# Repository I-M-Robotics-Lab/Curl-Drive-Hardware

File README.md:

# Curl-Drive: BLDC Motor Controller

This repository contains the hardware PCB design, schematics, and production files of the brushless motor FOC controller **Curl-Drive** developed by I'M Robotics Lab. 

The firmware is still under development, but the hardware has been validated with no major issues. Full version is planned to be released in early January. 

We welcome contributions from anyone! To get involved or ask questions, join our Discord server. 

Discord: https://discord.com/invite/WJuUWsy6DJ

Firmware (pre-release): https://github.com/I-M-Robotics-Lab/Curl-Drive-Firmware

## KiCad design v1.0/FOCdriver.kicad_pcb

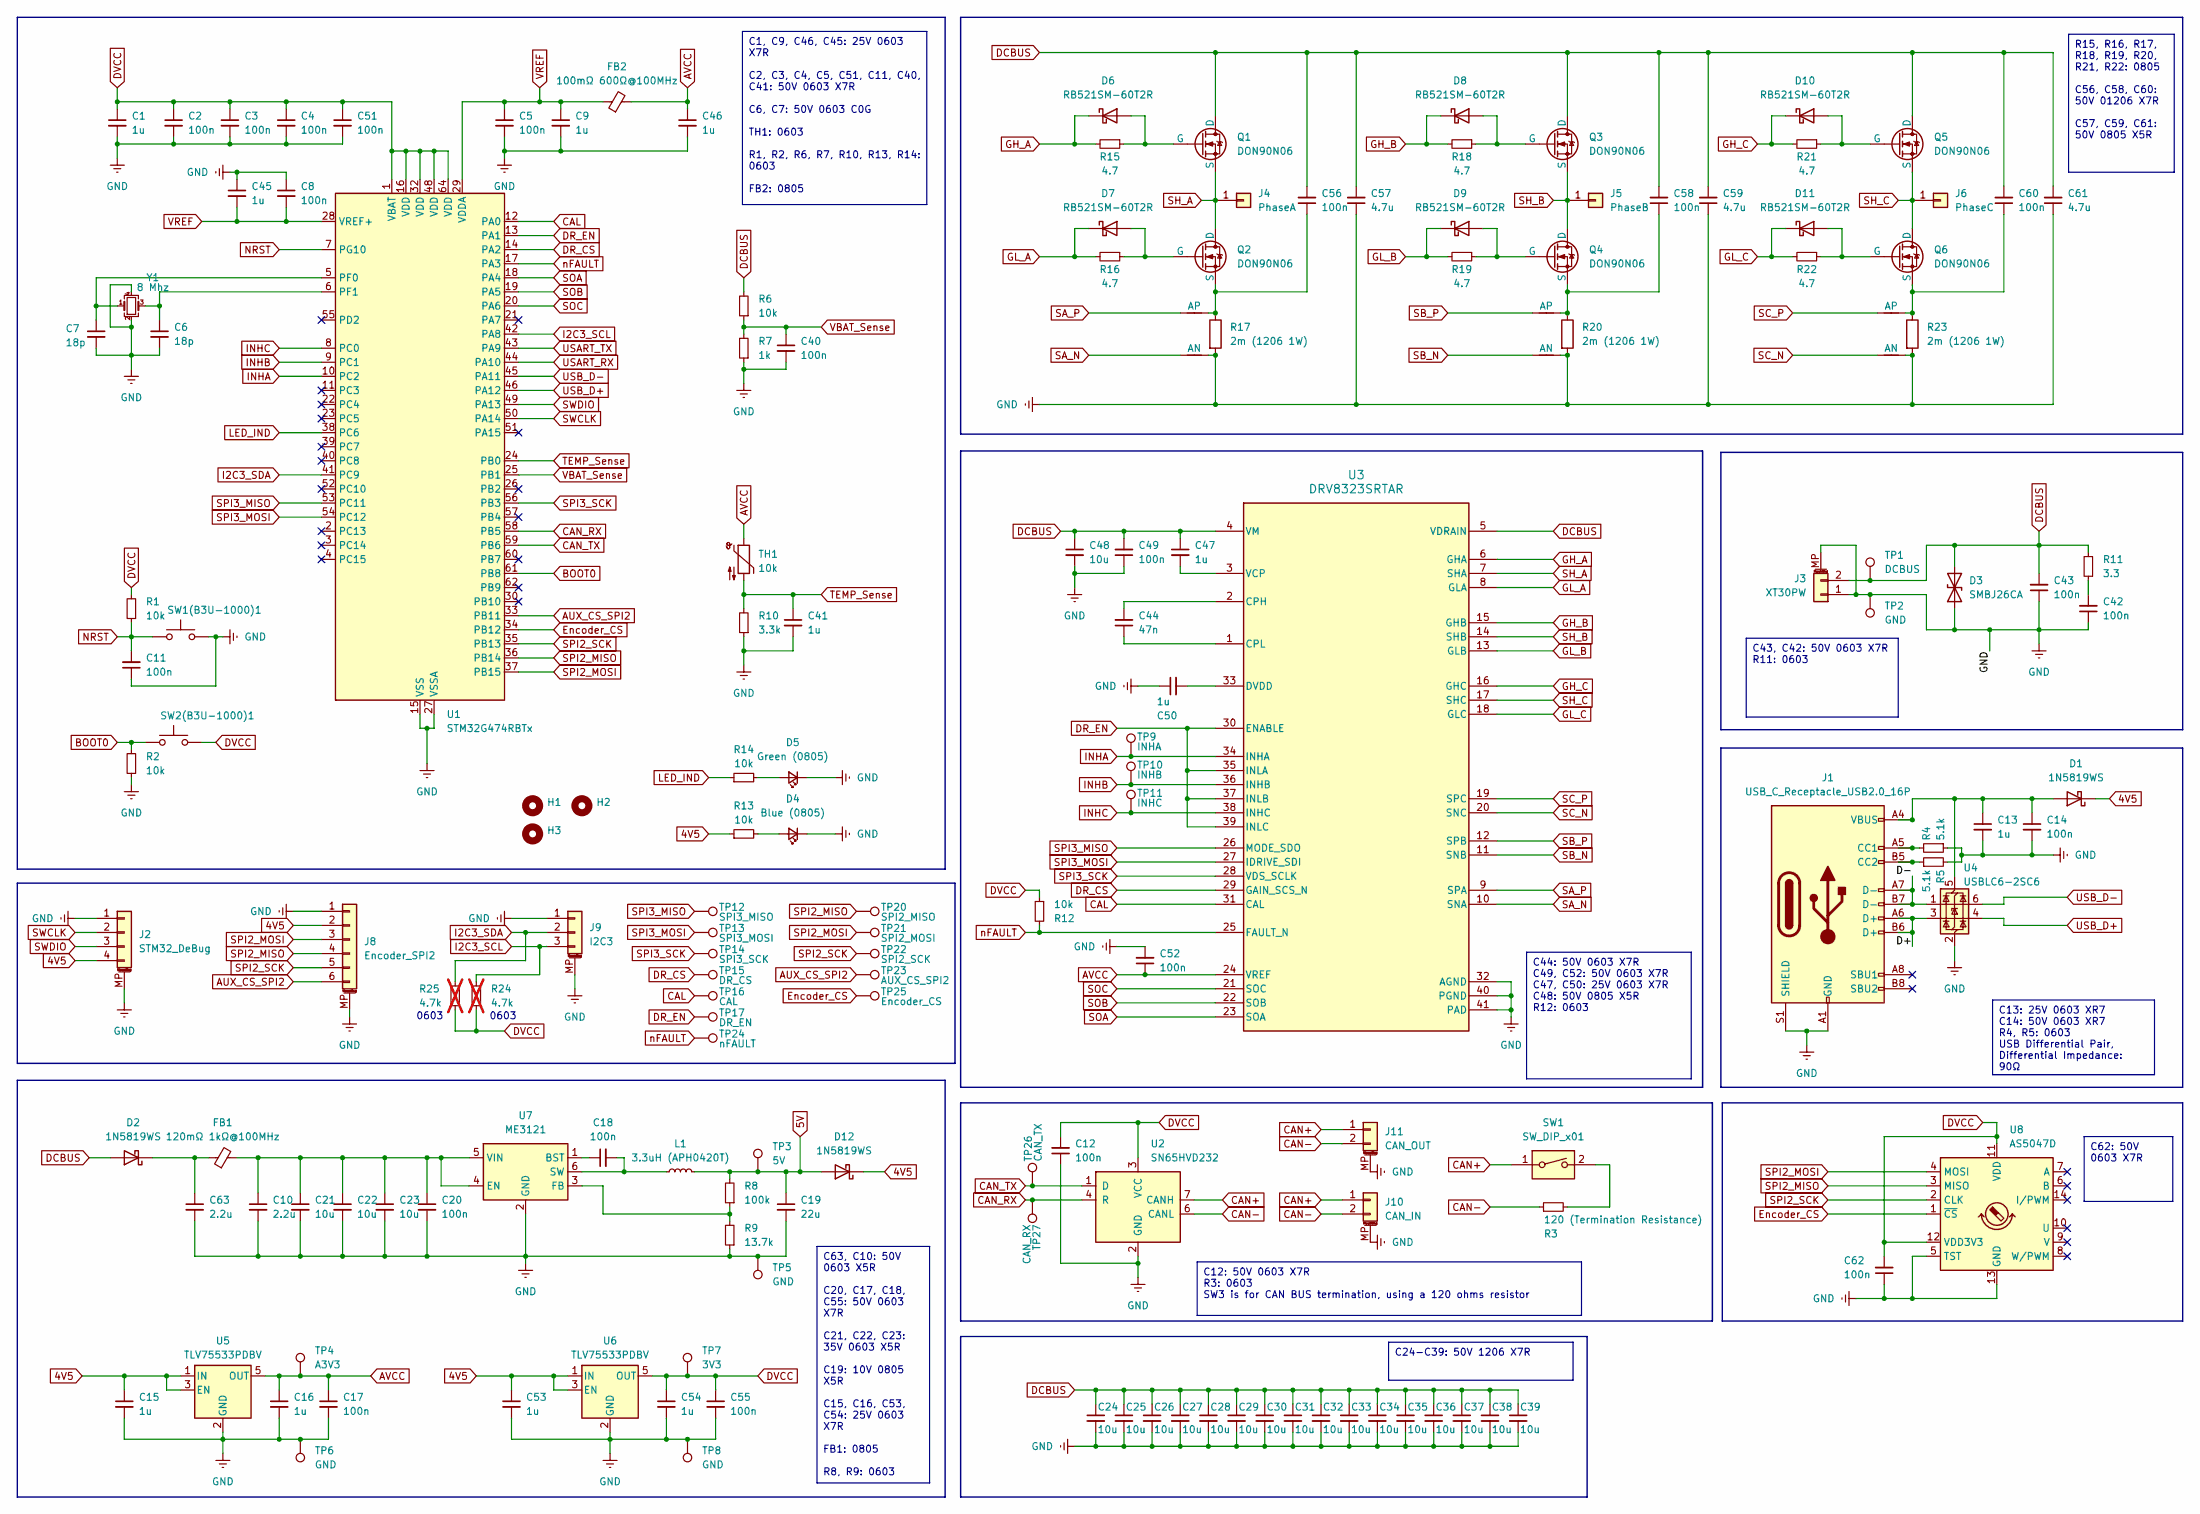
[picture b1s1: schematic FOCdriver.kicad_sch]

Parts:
C1, C9, C13, C15, C16, C41, C45, C46, C47, C50, C53, C54: 1u; C_0603_1608Metric
C2, C3, C4, C5, C8, C11, C12, C14, C17, C18, C20, C40, C42, C43, C49, C51, C52, C55, C62: 100n; C_0603_1608Metric
C6, C7: 18p; C_0603_1608Metric
C10, C63: 2.2u; C_0603_1608Metric
C19: 22u; C_0805_2012Metric
C21, C22, C23: 10u; C_0603_1608Metric
C24, C25, C26, C27, C28, C29, C30, C31, C32, C33, C34, C35, C36, C37, C38, C39: 10u; C_1206_3216Metric
C44: 47n; C_0603_1608Metric
C48: 10u; C_0805_2012Metric
C56, C58, C60: 100n; C_1206_3216Metric
C57, C59, C61: 4.7u; C_0805_2012Metric
D1, D2, D12: 1N5819WS; D_SOD-323
D3: SMBJ26CA; D_SMB
D4: Blue (0805); LED_0805_2012Metric
D5: Green (0805); LED_0805_2012Metric
D6, D7, D8, D9, D10, D11: RB521SM-60T2R; D_SOD-523
FB1: 120mΩ 1kΩ@100MHz; R_0805_2012Metric
FB2: 100mΩ 600Ω@100MHz; R_0805_2012Metric
H1, H2, H3: MountingHole_2.2mm_M2_DIN965_Pad
J1: USB_C_Receptacle_USB2.0_16P; USB_C_Receptacle_G-Switch_GT-USB-7010ASV
J2: STM32_DeBug; JST_SH_SM04B-SRSS-TB_1x04-1MP_P1.00mm_Horizontal
J3: XT30PW; AMASS_XT30PW-M_1x02_P2.50mm_Horizontal
J4: PhaseA; 4.5x4.5_pad
J5: PhaseB; 4.5x4.5_pad
J6: PhaseC; 4.5x4.5_pad
J8: Encoder_SPI2; JST_SH_SM06B-SRSS-TB_1x06-1MP_P1.00mm_Horizontal
J9: I2C3; JST_SH_SM03B-SRSS-TB_1x03-1MP_P1.00mm_Horizontal
J10: CAN_IN; JST_SH_SM02B-SRSS-TB_1x02-1MP_P1.00mm_Horizontal
J11: CAN_OUT; JST_SH_SM02B-SRSS-TB_1x02-1MP_P1.00mm_Horizontal
L1: 3.3uH (APH0420T); L_APV_APH0420
NT1, NT3, NT5: AP; NetTie-2
NT2, NT4, NT6: AN; NetTie-2
Q1, Q2, Q3, Q4, Q5, Q6: DON90N06; DFN-8-1EP_6x5mm_MOSFET
R1, R2, R6, R12, R13, R14: 10k; R_0603_1608Metric
R3: 120 (Termination Resistance); R_0603_1608Metric
R4, R5: 5.1k; R_0603_1608Metric
R7: 1k; R_0603_1608Metric
R8: 100k; R_0603_1608Metric
R9: 13.7k; R_0603_1608Metric
R10: 3.3k; R_0603_1608Metric
R11: 3.3; R_0603_1608Metric
R15, R16, R18, R19, R21, R22: 4.7; R_0603_1608Metric
R17, R20, R23: 2m (1206 1W); R_1206_3216Metric
R24, R25: 4.7k; R_0603_1608Metric; not fitted
SW1: SW_DIP_x01; SW_SPST_DSHP-01-TJ-GER
SW1(B3U-1000)1, SW2(B3U-1000)1: SW_Push; SW_SPST_B3U-1000P
TH1: 10k; R_0603_1608Metric
TP1: DCBUS; TestPoint_Pad_D0.4mm
TP2, TP5, TP6, TP8: GND; TestPoint_Pad_D0.4mm
TP3: 5V; TestPoint_Pad_D0.4mm
TP4: A3V3; TestPoint_Pad_D0.4mm
TP7: 3V3; TestPoint_Pad_D0.4mm
TP9: INHA; TestPoint_Pad_D0.4mm
TP10: INHB; TestPoint_Pad_D0.4mm
TP11: INHC; TestPoint_Pad_D0.4mm
TP12: SPI3_MISO; TestPoint_Pad_D0.4mm
TP13: SPI3_MOSI; TestPoint_Pad_D0.4mm
TP14: SPI3_SCK; TestPoint_Pad_D0.4mm
TP15: DR_CS; TestPoint_Pad_D0.4mm
TP16: CAL; TestPoint_Pad_D0.4mm
TP17: DR_EN; TestPoint_Pad_D0.4mm
TP20: SPI2_MISO; TestPoint_Pad_D0.4mm
TP21: SPI2_MOSI; TestPoint_Pad_D0.4mm
TP22: SPI2_SCK; TestPoint_Pad_D0.4mm
TP23: AUX_CS_SPI2; TestPoint_Pad_D0.4mm
TP24: nFAULT; TestPoint_Pad_D0.4mm
TP25: Encoder_CS; TestPoint_Pad_D0.4mm
TP26: CAN_TX; TestPoint_Pad_D0.4mm
TP27: CAN_RX; TestPoint_Pad_D0.4mm
U1: STM32G474RBTx; LQFP-64_10x10mm_P0.5mm
U2: SN65HVD232; SOIC-8_3.9x4.9mm_P1.27mm
U3: DRV8323SRTAR; DRV8323
U4: USBLC6-2SC6; SOT-23-6
U5, U6: TLV75533PDBV; SOT-23-5
U7: ME3121; SOT-23-6
U8: AS5047D; TSSOP-14_4.4x5mm_P0.65mm
Y1: 8 Mhz; Crystal_SMD_3225-4Pin_3.2x2.5mm

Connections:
4V5: C15.1, C53.1, D1.1 (K), D12.1 (K), J2.4, J8.2, R13.1, U5.1 (IN), U5.3 (EN), U6.1 (IN), U6.3 (EN)
5V: C19.1, D12.2 (A), L1.2, R8.2, TP3.1
/D+: J1.A6 (D+), J1.B6 (D+), U4.3 (I/O2)
/D-: J1.A7 (D-), J1.B7 (D-), U4.1 (I/O1)
AUX_CS_SPI2: J8.6, TP23.1, U1.33 (PB11)
AVCC: C16.1, C17.1, C46.1, C52.1, FB2.2, TH1.1, TP4.1, U3.24 (VREF), U5.5 (OUT)
BOOT0: R2.2, SW2(B3U-1000)1.1, U1.61 (PB8)
CAL: TP16.1, U1.12 (PA0), U3.31 (CAL)
CAN+: J10.1, J11.1, SW1.1, U2.7 (CANH)
CAN-: J10.2, J11.2, R3.1, U2.6 (CANL)
CAN_RX: TP27.1, U1.58 (PB5), U2.4 (R)
CAN_TX: TP26.1, U1.59 (PB6), U2.1 (D)
DCBUS: C24.1, C25.1, C26.1, C27.1, C28.1, C29.1, C30.1, C31.1, C32.1, C33.1, C34.1, C35.1, C36.1, C37.1, C38.1, C39.1, C43.2, C47.1, C48.1, C49.2, C56.2, C57.2, C58.2, C59.2, C60.2, C61.2, D2.2 (A), D3.2 (A2), J3.2, Q1.1 (D), Q3.1 (D), Q5.1 (D), R6.2, R11.2, TP1.1, U3.4 (VM), U3.5 (VDRAIN)
DR_CS: TP15.1, U1.14 (PA2), U3.29 (GAIN_SCS_N)
DR_EN: TP17.1, U1.13 (PA1), U3.30 (ENABLE), U3.35 (INLA), U3.37 (INLB), U3.39 (INLC)
DVCC: C1.1, C2.1, C3.1, C4.1, C12.2, C51.1, C54.1, C55.1, C62.2, R1.2, R12.1, R24.1, R25.1, SW2(B3U-1000)1.2, TP7.1, U1.1 (VBAT), U1.16 (VDD), U1.32 (VDD), U1.48 (VDD), U1.64 (VDD), U2.3 (VCC), U6.5 (OUT), U8.11 (VDD), U8.12 (VDD3V3)
Encoder_CS: TP25.1, U1.34 (PB12), U8.1 (~CS)
GH_A: D6.1 (K), R15.2, U3.6 (GHA)
GH_B: D8.1 (K), R18.2, U3.15 (GHB)
GH_C: D10.1 (K), R21.2, U3.16 (GHC)
GL_A: D7.1 (K), R16.2, U3.8 (GLA)
GL_B: D9.1 (K), R19.2, U3.13 (GLB)
GL_C: D11.1 (K), R22.2, U3.18 (GLC)
GND: C1.2, C2.2, C3.2, C4.2, C5.2, C6.2, C7.2, C8.1, C9.2, C10.2, C11.1, C12.1, C13.2, C14.2, C15.2, C16.2, C17.2, C19.2, C20.2, C21.2, C22.2, C23.2, C24.2, C25.2, C26.2, C27.2, C28.2, C29.2, C30.2, C31.2, C32.2, C33.2, C34.2, C35.2, C36.2, C37.2, C38.2, C39.2, C40.2, C41.2, C42.1, C43.1, C45.1, C46.2, C48.2, C49.1, C50.1, C51.2, C52.2, C53.2, C54.2, C55.2, C57.1, C59.1, C61.1, C62.1, C63.2, D3.1 (A1), D4.1 (K), D5.1 (K), H1.1, H2.1, H3.1, J1.A1 (GND), J1.A12 (GND), J1.B1 (GND), J1.B12 (GND), J1.S1 (SHIELD), J2.1, J2.MP (MountPin), J3.1, J3.MP (MountPin), J8.1, J8.MP (MountPin), J9.1, J9.MP (MountPin), J10.MP (MountPin), J11.MP (MountPin), NT2.2, NT4.2, NT6.2, R2.1, R4.1, R5.2, R7.1, R9.1, R10.1, R17.2, R20.2, R23.2, SW1(B3U-1000)1.2, TP2.1, TP5.1, TP6.1, TP8.1, U1.15 (VSS), U1.27 (VSSA), U1.31 (VSS), U1.47 (VSS), U1.63 (VSS), U2.2 (GND), U3.32 (AGND), U3.40 (PGND), U3.41 (PAD), U4.2 (GND), U5.2 (GND), U6.2 (GND), U7.2 (GND), U8.5 (TST), U8.13 (GND), Y1.2, Y1.4
I2C3_SCL: J9.3, R24.2, U1.42 (PA8)
I2C3_SDA: J9.2, R25.2, U1.41 (PC9)
INHA: TP9.1, U1.10 (PC2), U3.34 (INHA)
INHB: TP10.1, U1.9 (PC1), U3.36 (INHB)
INHC: TP11.1, U1.8 (PC0), U3.38 (INHC)
LED_IND: R14.1, U1.38 (PC6)
NRST: C11.2, R1.1, SW1(B3U-1000)1.1, U1.7 (PG10)
unnamed: C42.2, R11.1
unnamed: C13.1, C14.1, D1.2 (A), J1.A4 (VBUS), J1.A9 (VBUS), J1.B4 (VBUS), J1.B9 (VBUS), U4.5 (VBUS)
unnamed: C63.1, D2.1 (K), FB1.1
unnamed: D4.2 (A), R13.2
unnamed: D5.2 (A), R14.2
unnamed: D6.2 (A), Q1.2 (G), R15.1
unnamed: D7.2 (A), Q2.2 (G), R16.1
unnamed: D8.2 (A), Q3.2 (G), R18.1
unnamed: D9.2 (A), Q4.2 (G), R19.1
unnamed: D10.2 (A), Q5.2 (G), R21.1
unnamed: D11.2 (A), Q6.2 (G), R22.1
unnamed: J1.A5 (CC1), R4.2
unnamed: J1.B5 (CC2), R5.1
unnamed: C56.1, NT1.2, Q2.3 (S), R17.1
unnamed: C58.1, NT3.2, Q4.3 (S), R20.1
unnamed: C60.1, NT5.2, Q6.3 (S), R23.1
unnamed: R3.2, SW1.2
unnamed: C7.1, U1.5 (PF0), Y1.1
unnamed: C6.1, U1.6 (PF1), Y1.3
unnamed: C44.2, U3.2 (CPH)
unnamed: C44.1, U3.1 (CPL)
unnamed: C50.2, U3.33 (DVDD)
unnamed: C47.2, U3.3 (VCP)
unnamed: C18.1, U7.1 (BST)
unnamed: C10.1, C20.1, C21.1, C22.1, C23.1, FB1.2, U7.4 (EN), U7.5 (VIN)
unnamed: R8.1, R9.2, U7.3 (FB)
unnamed: C18.2, L1.1, U7.6 (SW)
SA_N: NT2.1, U3.10 (SNA)
SA_P: NT1.1, U3.9 (SPA)
SB_N: NT4.1, U3.11 (SNB)
SB_P: NT3.1, U3.12 (SPB)
SC_N: NT6.1, U3.20 (SNC)
SC_P: NT5.1, U3.19 (SPC)
SH_A: J4.1, Q1.3 (S), Q2.1 (D), U3.7 (SHA)
SH_B: J5.1, Q3.3 (S), Q4.1 (D), U3.14 (SHB)
SH_C: J6.1, Q5.3 (S), Q6.1 (D), U3.17 (SHC)
SOA: U1.18 (PA4), U3.23 (SOA)
SOB: U1.19 (PA5), U3.22 (SOB)
SOC: U1.20 (PA6), U3.21 (SOC)
SPI2_MISO: J8.4, TP20.1, U1.36 (PB14), U8.3 (MISO)
SPI2_MOSI: J8.3, TP21.1, U1.37 (PB15), U8.4 (MOSI)
SPI2_SCK: J8.5, TP22.1, U1.35 (PB13), U8.2 (CLK)
SPI3_MISO: TP12.1, U1.53 (PC11), U3.26 (MODE_SDO)
SPI3_MOSI: TP13.1, U1.54 (PC12), U3.27 (IDRIVE_SDI)
SPI3_SCK: TP14.1, U1.56 (PB3), U3.28 (VDS_SCLK)
SWCLK: J2.2, U1.50 (PA14)
SWDIO: J2.3, U1.49 (PA13)
TEMP_Sense: C41.1, R10.2, TH1.2, U1.24 (PB0)
USART_RX: U1.44 (PA10)
USART_TX: U1.43 (PA9)
USB_D+: U1.46 (PA12), U4.4 (I/O2)
USB_D-: U1.45 (PA11), U4.6 (I/O1)
VBAT_Sense: C40.1, R6.1, R7.2, U1.25 (PB1)
VREF: C5.1, C8.2, C9.1, C45.2, FB2.1, U1.28 (VREF+), U1.29 (VDDA)
nFAULT: R12.2, TP24.1, U1.17 (PA3), U3.25 (FAULT_N)

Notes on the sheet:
C63, C10: 50V 0603 X5R C20, C17, C18, C55: 50V 0603 X7R C21, C22, C23: 35V 0603 X5R C19: 10V 0805 X5R C15, C16, C53, C54: 25V 0603 X7R FB1: 0805 R8, R9: 0603
C62: 50V 0603 X7R
C13: 25V 0603 XR7 C14: 50V 0603 XR7 R4, R5: 0603 USB Differential Pair, Differential Impedance: 90Ω
R15, R16, R17, R18, R19, R20, R21, R22: 0805 C56, C58, C60: 50V 01206 X7R C57, C59, C61: 50V 0805 X5R
C43, C42: 50V 0603 X7R R11: 0603
C1, C9, C46, C45: 25V 0603 X7R C2, C3, C4, C5, C51, C11, C40, C41: 50V 0603 X7R C6, C7: 50V 0603 C0G TH1: 0603 R1, R2, R6, R7, R10, R13, R14: 0603 FB2: 0805
C24-C39: 50V 1206 X7R
C44: 50V 0603 X7R C49, C52: 50V 0603 X7R C47, C50: 25V 0603 X7R C48: 50V 0805 X5R R12: 0603
C12: 50V 0603 X7R R3: 0603 SW3 is for CAN BUS termination, using a 120 ohms resistor
0603

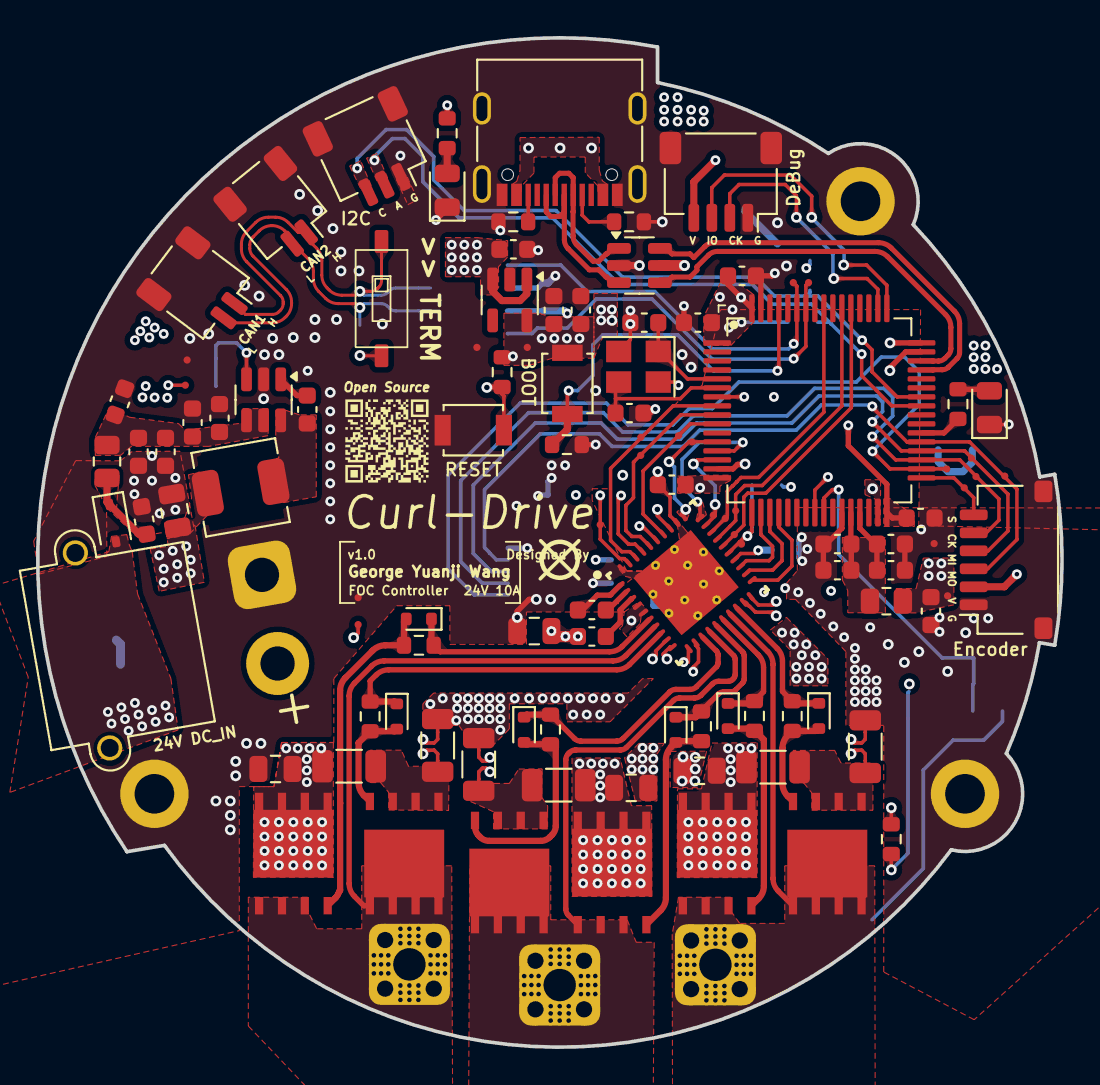
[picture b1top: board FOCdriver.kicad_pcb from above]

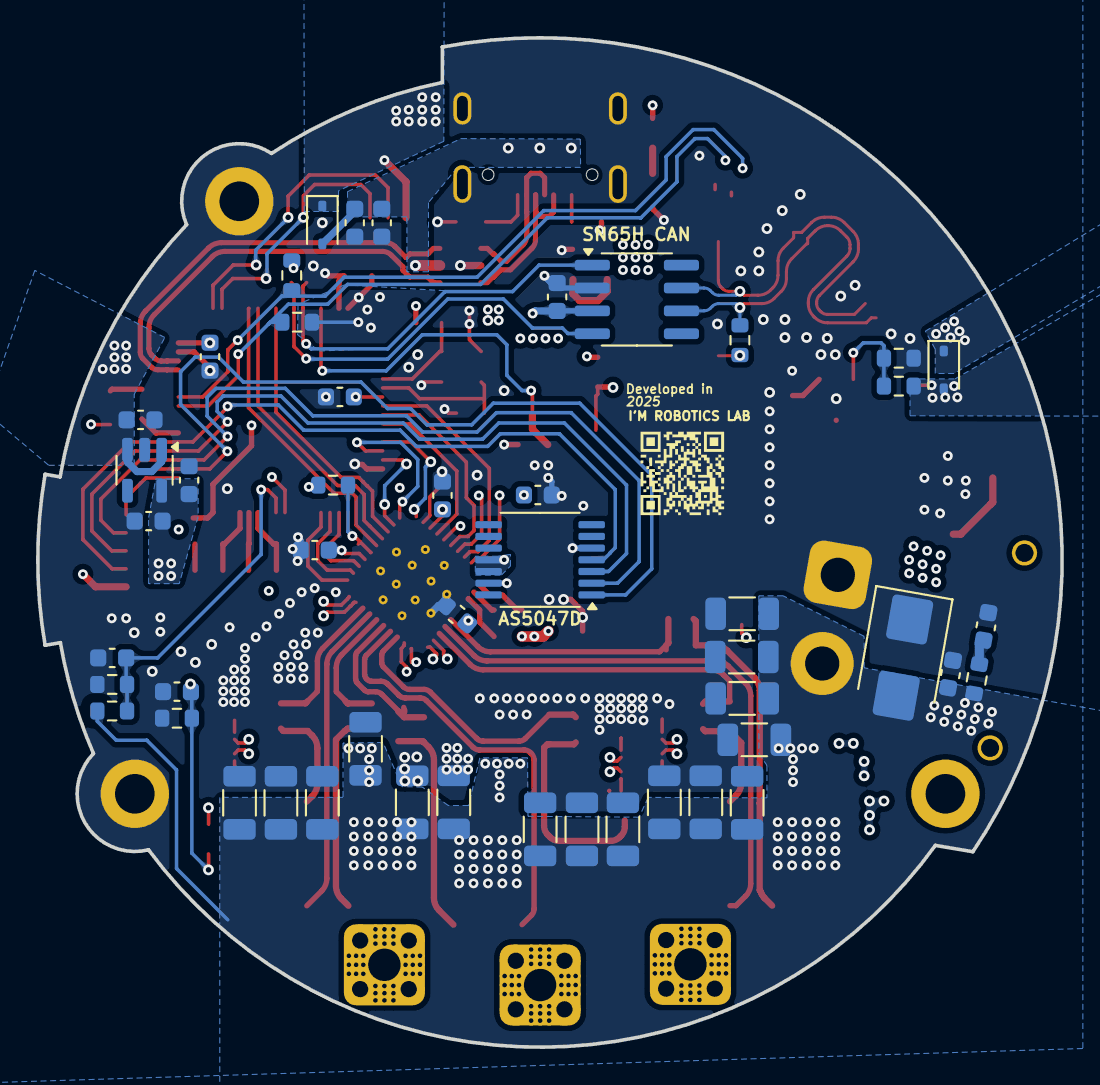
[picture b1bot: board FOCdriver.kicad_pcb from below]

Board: 4 copper layers, 56.9 x 56.1 mm, 166 parts (48 on the bottom side), 84 nets.

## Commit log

2025-11-10 add license
2025-11-13 schematics
2026-01-07 Change firmware release date in README
    Updated the expected firmware release date from early December to early January.
2026-02-04 Add firmware link to README
